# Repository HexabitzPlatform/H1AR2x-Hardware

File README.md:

# H1AR2x-Hardware
Hexabitz Mini USB-B-to-UART Converter Module Hardware Design

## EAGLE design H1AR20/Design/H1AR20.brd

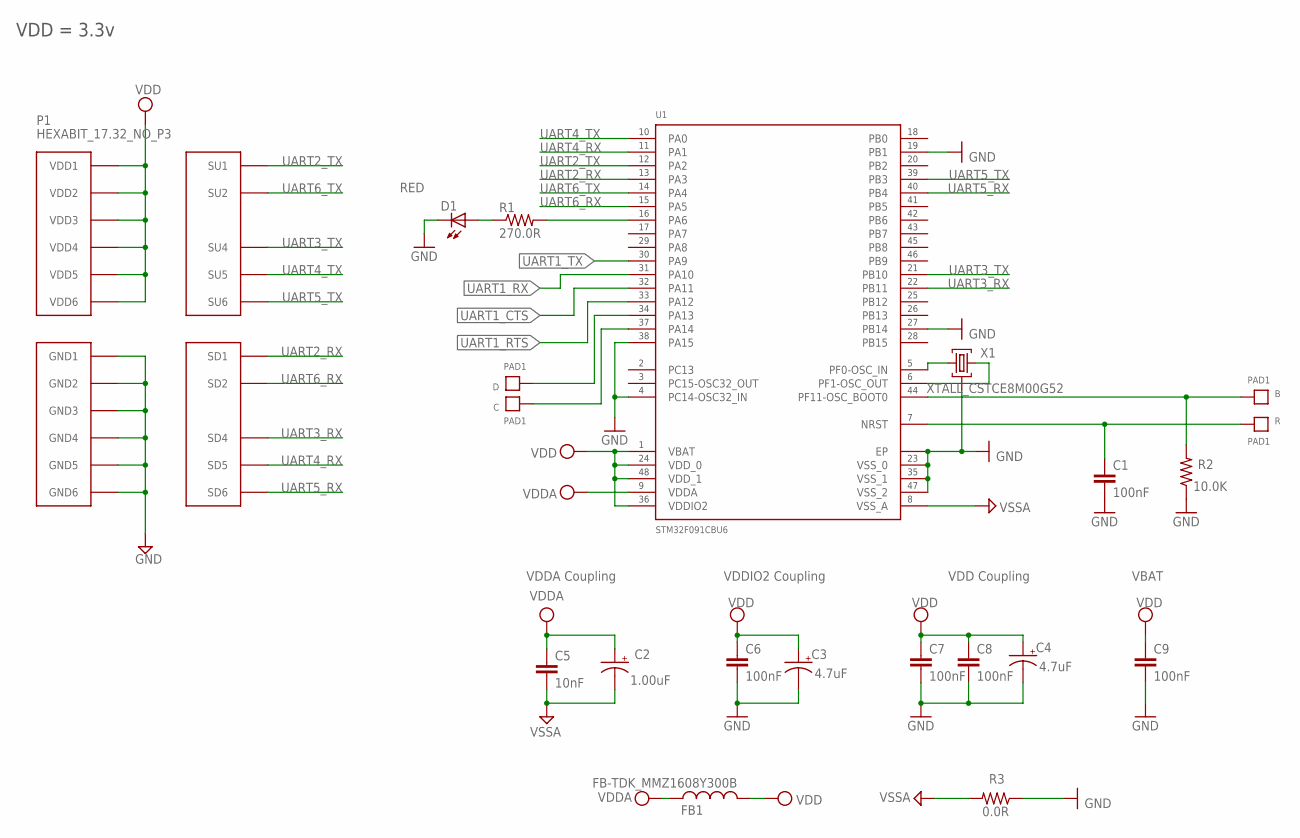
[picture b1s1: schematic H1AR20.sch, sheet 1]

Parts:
B: PAD1
C: PAD1
C1, C6, C8: 100nF; C-0603; TOLERANCE 10%; VOLTAGE_RATING 10V; MPN C0603C104K8RACTU
C2: 1.00uF; C-0805-POL; TOLERANCE 10%; VOLTAGE_RATING 16V; MPN CC0805KKX7R7BB105
C3, C4: 4.7uF; C-0805-POL; TOLERANCE 10%; VOLTAGE_RATING 25V; MPN GRM21BC81E475KA12L
C5: 10nF; C-0603; TOLERANCE 10%; VOLTAGE_RATING 50V; MPN C0603C103K5RACTU
C7: 100nF; C-0603; TOLERANCE 10%; VOLTAGE_RATING 10; MPN C0603C104K8RACTU
C9: 100nF; C-0603; TOLERANCE 10V; VOLTAGE_RATING 10%; MPN C0603C104K8RACTU
D: PAD1
D1: RED; VLMS1300-GS08; MPN VLMS1300-GS08
FB1: FB-TDK_MMZ1608Y300B; MPN MMZ1608Y300B
P1: HEXABIT_17.32_NO_P3
R: PAD1
R1: 270.0R; R-0603; TOLERANCE 1%; MPN RC0603FR-07270RL
R2: 10.0K; R-0603; TOLERANCE 5%; MPN CRCW060310K0JNEB
R3: 0.0R; R-0603; MPN RC0603JR-070RL
U1: STM32F091CBU6
X1: XTALL_CSTCE8M00G52

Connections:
B1: B.P$1, B.P$2, R2.2, U1.P$44 (PF11-OSC_BOOT0)
GND: C1.2, C3.2 (-), C4.2 (-), C6.2, C7.2, C8.2, C9.2, D1.C, P1.PAD_PD7 (GND1), P1.PAD_PD8 (GND2), P1.PAD_PD9 (GND3), P1.PAD_PD10 (GND4), P1.PAD_PD11 (GND5), P1.PAD_PD12 (GND6), R2.1, R3.1, U1.EP, U1.P$3 (PC14-OSC32_IN), U1.P$19 (PB1), U1.P$23 (VSS_0), U1.P$27 (PB14), U1.P$35 (VSS_1), U1.P$38 (PA15), U1.P$47 (VSS_2), X1.P$2 (2); also elsewhere on the board
unnamed: R1.2, U1.P$16 (PA6)
unnamed: D1.A, R1.1
unnamed: U1.P$5 (PF0-OSC_IN), X1.P$1 (1)
unnamed: U1.P$6 (PF1-OSC_OUT), X1.P$3 (3)
unnamed: D.P$1, D.P$2, U1.P$34 (PA13)
unnamed: C.P$1, C.P$2, U1.P$37 (PA14)
R1: C1.1, R.P$1, R.P$2, U1.P$7 (NRST)
UART1_CTS: U1.P$32 (PA11); also elsewhere on the board
UART1_RTS: U1.P$33 (PA12); also elsewhere on the board
UART1_RX: U1.P$31 (PA10); also elsewhere on the board
UART1_TX: U1.P$30 (PA9); also elsewhere on the board
UART2_RX: P1.PAD_PD1 (SD1), U1.P$13 (PA3)
UART2_TX: P1.PAD_PU1 (SU1), U1.P$12 (PA2)
UART3_RX: P1.PAD_PD4 (SD4), U1.P$22 (PB11)
UART3_TX: P1.PAD_PU4 (SU4), U1.P$21 (PB10)
UART4_RX: P1.PAD_PD5 (SD5), U1.P$11 (PA1)
UART4_TX: P1.PAD_PU5 (SU5), U1.P$10 (PA0)
UART5_RX: P1.PAD_PD6 (SD6), U1.P$40 (PB4)
UART5_TX: P1.PAD_PU6 (SU6), U1.P$39 (PB3)
UART6_RX: P1.PAD_PD2 (SD2), U1.P$15 (PA5)
UART6_TX: P1.PAD_PU2 (SU2), U1.P$14 (PA4)
VDD: C3.1 (+), C4.1 (+), C6.1, C7.1, C8.1, C9.1, FB1.2, P1.PAD_PU7 (VDD1), P1.PAD_PU8 (VDD2), P1.PAD_PU9 (VDD3), P1.PAD_PU10 (VDD4), P1.PAD_PU11 (VDD5), P1.PAD_PU12 (VDD6), U1.P$1 (VBAT), U1.P$24 (VDD_0), U1.P$36 (VDDIO2), U1.P$48 (VDD_1); also elsewhere on the board
VDDA: C2.1 (+), C5.1, FB1.1, U1.P$9 (VDDA)
VSSA: C2.2 (-), C5.2, R3.2, U1.P$8 (VSS_A)

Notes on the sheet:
VDDA Coupling
VDDIO2 Coupling
VDD Coupling
VBAT
VDD = 3.3v

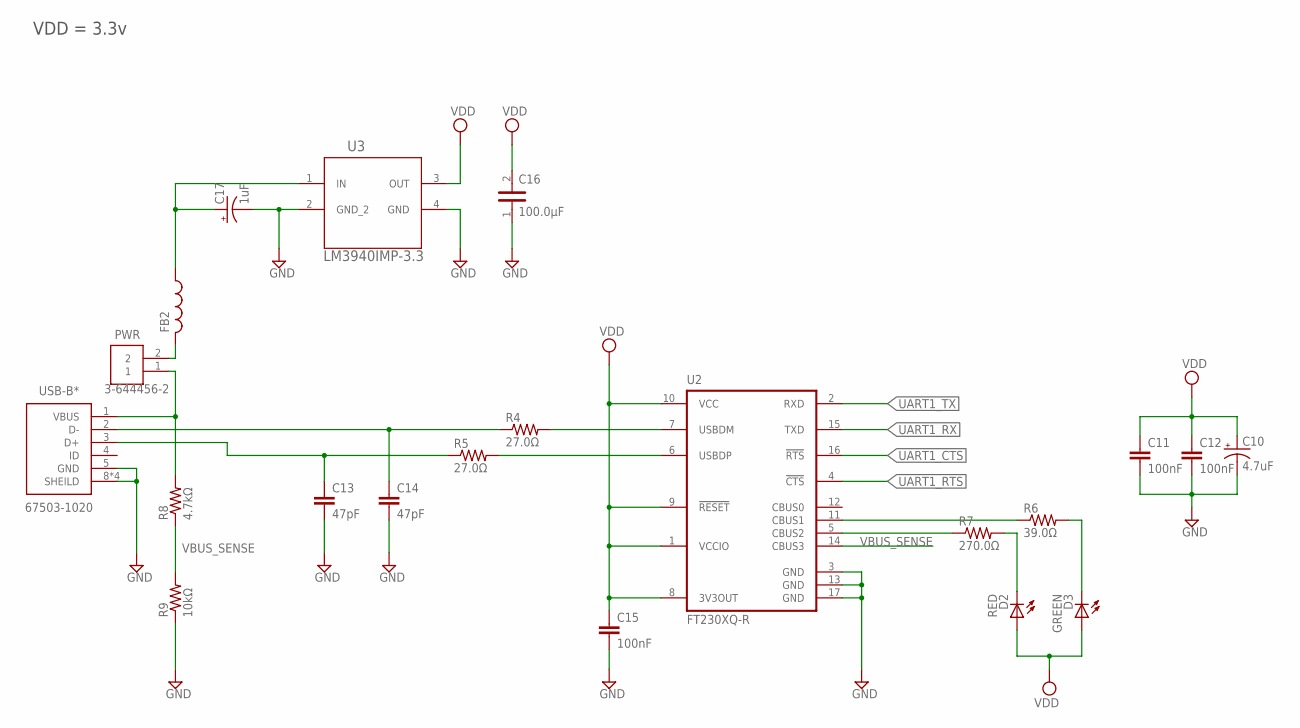
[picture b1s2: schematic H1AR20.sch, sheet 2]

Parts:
C10: 4.7uF; C-0805-POL; TOLERANCE ±20%; VOLTAGE_RATING 10.0 V; MPN 10TPU4R7MSI
C11, C12, C15: 100nF; C-0603; TOLERANCE ±10%; VOLTAGE_RATING 16.0 V; MPN 0603YC104K4T2A
C13, C14: 47pF; C-0603; TOLERANCE ±5%; VOLTAGE_RATING 50.0 V; MPN 06035A470JAT2A
C16: 100uF; C-3225
C17: 1uF; C-0805-POL; TOLERANCE ±20%; VOLTAGE_RATING 16.0 V; MPN TAJR105M016RNJ
D2: RED; VLMS1300-GS08
D3: GREEN; VLMS1300-GS08
FB2: FB-TDK_MMZ1608Y300B; MPN MMZ1608Y300B
PWR: 3-644456-2; TE_3-644456-2
R4, R5: 27.0Ω; R-0603; TOLERANCE ±1%; MPN CRCW060327R0FKEA
R6: 39.0Ω; R-0603; TOLERANCE ±5%; MPN ERJ-3GEYJ390V
R7: 270.0Ω; R-0603; TOLERANCE ±5%; MPN ERJ-3GEYJ271V
R8: 4.7kΩ; R-0603; TOLERANCE ±1%; MPN CRCW06034K70FKEA
R9: 10kΩ; R-0603; TOLERANCE ±5%; MPN CRCW060310K0JNEB
U2: FT230XQ-R; QFN16
U3: LM3940IMP-3.3; SOT230P696X180-4N
USB-B*: 67503-1020

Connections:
GND: C10.2 (-), C11.2, C12.2, C13.2, C14.2, C15.2, C16.1, C17.2 (-), R9.1, U2.3 (GND), U2.13 (GND), U2.17 (GND), U3.2 (GND_2), U3.4 (GND), USB-B*.5 (GND), USB-B*.8 (SHEILD), USB-B*.9 (SHEILD), USB-B*.10 (SHEILD), USB-B*.11 (SHEILD); also elsewhere on the board
unnamed: C14.1, R4.1, USB-B*.2 (D-)
unnamed: C13.1, R5.1, USB-B*.3 (D+)
unnamed: FB2.2, PWR.2
unnamed: C17.1 (+), FB2.1, U3.1 (IN)
unnamed: R5.2, U2.6 (USBDP)
unnamed: R4.2, U2.7 (USBDM)
unnamed: R7.1, U2.5 (CBUS2)
unnamed: R6.1, U2.11 (CBUS1)
unnamed: D2.C, R7.2
unnamed: D3.C, R6.2
unnamed: PWR.1, R8.2, USB-B*.1 (VBUS)
UART1_CTS: U2.16 (!RTS!); also elsewhere on the board
UART1_RTS: U2.4 (!CTS!); also elsewhere on the board
UART1_RX: U2.15 (TXD); also elsewhere on the board
UART1_TX: U2.2 (RXD); also elsewhere on the board
VBUS_SENSE: R8.1, R9.2, U2.14 (CBUS3)
VDD: C10.1 (+), C11.1, C12.1, C15.1, C16.2, D2.A, D3.A, U2.1 (VCCIO), U2.8 (3V3OUT), U2.9 (!RESET!), U2.10 (VCC), U3.3 (OUT); also elsewhere on the board

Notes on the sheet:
VDD = 3.3v

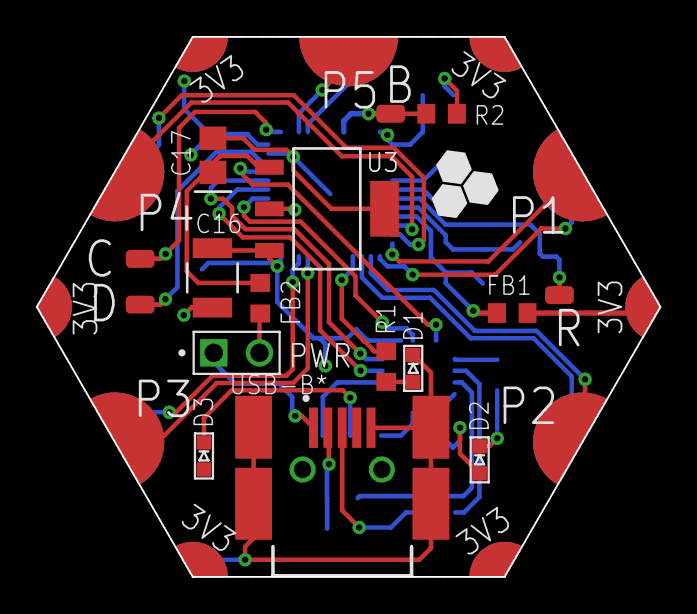
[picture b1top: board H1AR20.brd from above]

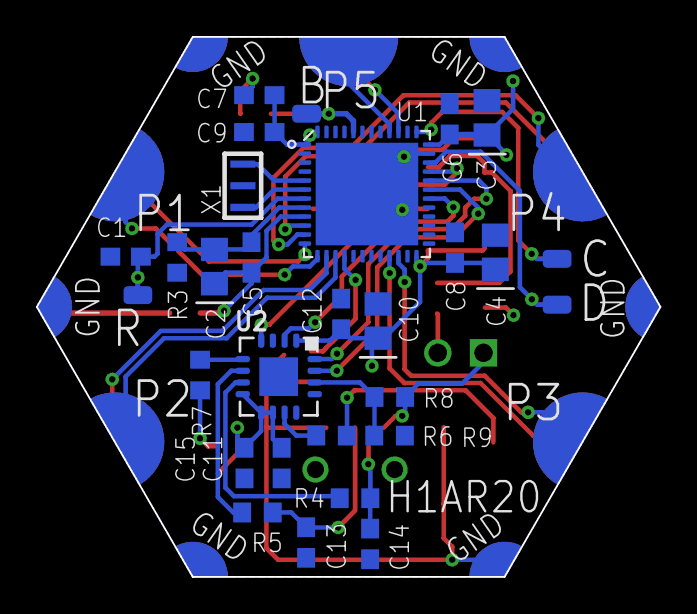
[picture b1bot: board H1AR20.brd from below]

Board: 2 copper layers, 34.6 x 30.0 mm, 42 parts (25 on the bottom side), 38 nets.

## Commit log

2020-03-01 Add template files
2020-03-03 In this update: - schematic is done - Attributes are assigned - BOM was generated
2020-03-03 - renamed res and cap to match the original Circuitmaker design - fixed BOM file according to changes
2020-03-03 replaced labels "USART" with "UART"
2020-03-08 - PCB is done - Generated all output files
2020-03-09 Remove temp files
2020-03-12 Minor PCB improvements
2020-03-16 minor changes in PCB..
2020-03-16 fixed BOM
2020-03-16 replaced (USB-B*) with (PUSB*) and fixed gerber files
2020-03-17 Move output files and rename schematics PDF. Release 0
2020-04-07 changed LED's colors, updated BOM and PDF schematic
2020-04-07 deleted annoying files
